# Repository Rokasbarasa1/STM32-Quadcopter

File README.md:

I am making a quadcopter from scratch (firmware including). This is the second step after my [Self balancing robot](https://github.com/Rokasbarasa1/ESP32-self-balancing-robot) project. It is still a work in progress, but a lot of the heavy lifting has already been done.

### Some features:
* Acro and Angle modes.
* GPS position hold flight mode (Work in progress).
* Altitude hold flight mode (Work in progress).
* Controled by my custom [Pi-pico based remote control](https://github.com/Rokasbarasa1/Pi-Pico-remote-control). 

### Sensors and hardware used for controller:
* Controller mcu - STM32F411
* Accelerometer + Gyro - MPU6050
* Magnetometer - MMC5603 (Used QMC5883 before)
* GPS - HGLRC M100 5883 (Used BN357 before)
* Barometer - MS5611 (Used BMP280 before)
* Radio link - RadioMaster RP1 2.4GHz ELRS (Work in progress)
* Debug Radio communication - NRF24l01
* Logging - [My custom STM32F411 based SD Logger](https://github.com/Rokasbarasa1/Logger). 

### Hardware of the drone itself:
* Motors - 4 x EMAX ECO II Series 2807 Motor
* ESC's - 4 x HGLRC 30amp 3-5S Dshot600 BLHeli_S 16.5 BB2 ESC (F-H-40 flashed with BlueJay 0.21.0V for BDshot600)
* Proppelers - 4 x HQProp DP 7x3.5x3 V1S 3 blade Propeller
* Battery - CNHL Black Series 3200mAh 14.8V 30C 4S (also used Turnigy 2200mAh 3S 25C)

# Latest flight video (January 2025)

# Pictures (Outdated)

### Checklist for going testing
* Drone frame
* Controller
* Controller antenna
* Propellers
* Sd card adapter
* Micro sd card
* Pliers 
* Wire cutters
* Screwdriver 
* Screwdriver bits
* Remote control
* Laptop
* Usb extension cable
* STM32 programmer
* Charged battery
* Battery checker

# Design documentation (work in progress)

## Code diagram

## Controller 

The controller is the main piece of the system. It is much more limited in what it can do than a normal computer, it is smaller, slower and resource constrained. So it cannot run a full GUI operating system. The good thing about them is that they are cheap and, depending on which one you get, just powerful enough to do interesting things. They are also cheap, I got mine for 7.28 USD. The microcontroller itself is just a chip on the breadboard. It is very self sufficient, sometimes you can just supply them stable power and they work fine. Like the attiny85 that just plugs into a breadboard. 

We need one that is more powerful than that so we will go with one called the STM32F411. ST(M)icroelectronics is the manufacturer, the 32 bit is how big data chunks the system can handle, and the F stands mainstream performance line of their chips, 411 is just a serial number for features. We dont really care about the features that much, it is maninstream so it will work for most things. 

I went with a ST microcontroller as it was one I had not used before. The chip on this one is very small so it is mounted on a pcb to seperate the tiny pins on the chip into big pins that we can use. The PCB that it is mounted on gives the microcontroller name blackpill because its a black pcb and its small. The pcb also has some extra features like voltage regulators to protect the chip, external oscillators to speed it up and leds to help us indicate status later. The pcb is so small that it lacks some quality of life features that a big pcb would have, like a programmer. The chip has to instead be programmed usng another product of ST called ST-link V2, which just converts a Usb interface to a programming interface for the stm32, it uses 4 pins to do that. This is negative of ST's products, other manufacturers dont have this problem with small pcb's, most of the time. The upside is you can debug the code with the same product, this is something that is painful on other microcontroller brands. The small form factor of the pcb is also very helpful for integrating the microcontroller into projects.

Each microcontroller manufacturer has their own "library" that abstracts the difficullt hardware drivers (HAL), on top of which the coding of the microcontroller can be done. In the case of the STM32 it is STM32Cube which lets you use C or C++ to write code for it. You can use Rust or anything else to write the code but then you are not using the manufacturers libraries and have to relly on open source. In my case I went with C as it is very simple and I can get great performance out of it. 

<!-- 
_The STM32F411 has a lot more GPIO than ESP32, which maybe has half of its pins unavailable and a bit more than the Pi-Pico on which a lot of the pins are grounds. Its also easier to mount on a breadboard than the ESP32._

_I hate the CubeMX code generation, feels like there is just junk in my repo. The alternative is really badly documented, to the point of needing to go into the library code to figure out how to use it. Feels like they skimped out on actual documentation to make you use the shitty code gen. Using the library code to figure something out is not easy either as there are multiple functions with similar names or functions that are depreceated. It always confusing to set anything up from scratch, like spi or i2c, there are so many functions that are supposed to do the exact same thing. By far the worst experiance of developing embededd software. Even fucking atmelavr felt like butter compared to this, though that might be a high bar in the embedded world. You cannot have development velocity in this ecosystem if you touch even a bit of the ST library. ESP32, Pi-pico and atmega are a lot better at this._

_Flashing the firmware on it is a lot easier though, in cases. If i was working on a breadboard, the Pi-pico would be a lot easier. When i made a protective cover for the controller part of the drone it was easy to press the pins of the programmer agains unsoldered holes of the pcb for programming. I did not have to fish for the 4 pins to attach too. This meant that sometimes the programming would not work, but overall it was a good experiance._

_For performance the STM32 is deffinetely not as fast as the ESP32, but it is fast enough, most of the performance is lost on sensor communication anyway._
-->

<!--
### Code design decisions

_The code looks not as a usual developers code looks like. I like having full names of the variables, no such bullshit as dT for delta time or whatever one letter variable. The same is for functions, full verbose names. I like to come back to old features and understand what is happenning. Lots of comments also._ 

_If there was a "Prettier" implementation for C (C code formaters are garbage, all of them) I would use it to enforce the same syntax everywhere, but there is not so there are gaps. I would love to enforce breaking of function variables if the developer has broken at least one, curly braces in line with for loops and if statments and functions.

_I tried to seperate the code into modules, of radio, data getting, motor control/pid and logging. They need to be moved to different files like controller/services/models architecture on backends, but at the moment it is just so much easier to have everything logic related in one file. In the future will be, main.c/business logic/drivers, with main.c only being able to reach drivers if it goes trough business logic. I come from full-stack development and we have much better understanding of code organization than embedded developers. The code will be seperated into seperate files once I am done with the project. I dont care about clean code, the functions will not be made 5 lines long._
-->

## Sensors drivers
To make our drone sense the world around it we need sensors. Based on the output of these sensors the code that i wrote in the microcontroller will make decisions and perform further actions to manipulate the environment it is in.

<!--
_A note about the sensor driver implementation. I continued the use of enums for defining the registers of the sensor and so on. Makes reading of the sensor code and even configuration of it a lot easier._

_Usage of macros for constant definitions is also done now. No more magic numbers, they have names now. Some pre division of these values is also done._
-->
### Supplying power to sensors
These sensors that we will talk about and hardware are meant to be powered some way, unless they have a battery on board them they have to have a physical connection to a power source. This is usually 2 wires, one for ground and one for most commonly 3.3V or 5V. A lot of the older snesors use 5V, these are usually the sensors made for the microcontroller called Arduino. These sensors need 5V because the old Arduino uses 5V logic(5V for a set bit and a 0V for a not set bit). If communication needs to be done to the sensor then there will always be a minimum of 2 wires or there can be more to accomodate different methods of sending or receiving information relating to the sensors. In the case where something has its own power source, and you know the power source or at least the interface that you will be using utilizes the voltage that is the same as you are using, then connecting the ground wire is enough. In fact if the device you are connecting to uses a different voltage than yours it is also safe to connect your ground to its ground. The important thing to match is the voltage lines, 5V, 12V, 15V.  

### Communcication to sensors
The sensors are just little microcontrollers in most cases, they have logic and interfaces that let the data be extracted from them digitally(toggling a single pin or more from 3.3v to 0V). There are sensors that are analog, but we are not using them, they are harder to work with. There are many methods of extracting the data out of sensors, these are called protocols. Each protocol has its advantages and disadvantages. Different combinations of, speed, wire count and complexity in setting it up. I will not be bothered to get into the details of how each protocol works as there are actual books for that. The best way to see how it works though is by getting thing called a "logic analyzer" and seeing for yourself how your hardware works.

#### I2C
I2C is one of the most convenient protocols to settup, it uses two wires, one for data and one for clock signal, it can also be chained to multiple sensors/device. Its fast enough and you can go above the recomended speeds if you believe in your hardware setup. I used I2C on my self-balacning robot project for sensors and it was fine. I did that again on this project and that was a mistake. You have to understand unless you are setting up something fancy to not have to do the communication to sensors synchronously, I2C can waste a lot of time by not being the fastest method.

I2c is very easy to setup though, and rarely ever causes problems. On the STM32 i did find that interrupts (will talk about these later) have to be disabled for the communication to not break. When it did break it would take 100ms to error out and continue with the program, essentially breaking the whole flow of the time sensitive program.

#### SPI
SPI is a lot harder to setup than I2c. The devices that can be communicated to using this have to have a slave select pin, that when 0V is applied to it means that the device is being communicated with. It also has 3 other pins, one for clock, one for data coming to slave and one for data coming to master. When you try to setup the hardware for a SPI connection, there is always something that just does not work. Its like having to plug in a usb, you always do it wrong way first. Sometimes the slaves/sensors have an extra pin that is also names similar to the slave select pin causing additonal confusion. The benefit of SPI is the speed it can reach, if you really need to be at the peak of performance then this is what you need. There are even variations of the protocol that use double or quadruple the pins amounts for the slave-master pins to multiply the transmission speed.

SPI is also a very simple protocol that you can even implement yourself. That cannot be said about I2C.

#### UART 
UART is the last protocol we actually care about and is one that is not normally used for sensors, but for transmitting text information or large amounts of data. It is also a very simple protocol, it uses 2 pins and does not use a clock pin. It  also cannot be chained like I2C and it is most importantly asynchronous by default. It is considered slower than the other protocols but it has benefits. It is reliable over long distances of wire and has recover mechanisms 

### I2C and sensors in general
For this communication we will use I2C. I2c is just a recipe (protocol) for what way to toggle the pins and in what order that both the controller trying to get the data (master) and the sensor (slave) understand and adhere to. There are other protoocls as well that the sensors support, like SPI, but I chose this one because it is easier to deal with. I2c uses only 4 wires, 2 for data. I2c is usually used for sensors or things that dont nescessarily need max speed in communication. You sacrifice speed for ease of communication.

### UART
Uart is another protocol for communication. It again uses 4 wires 

To do things with a sensor you need to read its datasheet. The most important part of which is the register map, it tells you where everything is stored and what register addresses you need to give to the sensor to read out the data from the registers. With i2c this often looks like sending the address of the register then reading the number of bytes you expect the data to be. Sometimes these sensors dont just automatically fill up their registers with data and you need to actually send commands that trigger actions that fill up populate those registers. Sometimes these commands just activate some special ability of the sensor. Thes sensors are almost always configurable in the same way also, by sending what register you want to fill up and then sending the bytes of data you want to put in that register. Configuring the sensor can be though of as having a wall of switches (the register map). There are as many rows of switches on it and the rows correspond to registers, each row has a number of switches that correspond to how large the register is in bits (most often its 8 bits). Each switch in the row does something, each one has a long description of its functionality in the datasheet. Some of the rows of switches you cannot manipulate as they are the ones storing the measurement that the sensor does, so the analogy falls appart there.

It should be noted that sensor data should never be taken as reliable data, the sensor data by default is always miscalibrated and has noise in it that makes judgements based on the data difficult. Each sensor type also has some problem that makes complex systems development difficult, but there are solutions to this, that we will talk about in sections "sensor fusion" and "filtering".

<!--
_I should have not used the I2c bus anymore in this project, for any of the sensors, its a bit too slow. I went above the recomended bus frequency though and reached 1.6 MHz but went down to 1.0 Mhz for stability just in case. That saved quite a of cpu time._
-->
# Gyro
The gyro can tell how fast the drone is rotating in each axis. If you tilt the drone 90 degrees to be on its side after it was standing flat on the ground and you do it immediately in one second the gyro will tell you that it degrees per second rotation is 90 on that axis you were rotating it around. To understand this, imagine a swing set attached to a metal pipe, the way the pipe is laying is some axis, lets say x, so the pipe is in line with the x axis. When you swing in the swing set you are really just rotating around the x axis of the pipe.

The gyro is the most important sensor for a drone. Depending on your requirements for the drone, it may be the only sensor you need, specifally for a mode control for the drone called acro mode. We will be implementing this mode of control but also more.
DRIFT

I am using the gyro on a sensor module called MPU6050. It is a common sensor, used on many drones. It actually has an accelerometer on it as well, but that is for later. The MPU6050 chip itself is mounted on a pcb that has voltage control stuff and power stabilization capacitors on it. This makes working with it easier, low risk of frying due to high voltage and it should be isolated from the power disturbances that can happen in an embedded system (these can just make the sensor not work very good). 

The sensor itself is configured by the code to be able to sense a max of 500 dps/s of rotation, which should be plenty for our drone if we dont plan to do spinny tricks in acro mode.

The gyro does have a problem. You may think if you keep summing the dps data over time, that you will get some data that tells you the orientation of the drone in 3D space, but that is not going to happen. The Gyro data is inherently noisy and if you sum it you will get values that drift over time. You can ease this noise issue by calibrating the gyro. Which is just reading maybe 1000 gyro values while sitting still and, finding the average gyro output value and then every time the you get the value out of the sensor you substract that average value from the data. This effectively removes some of the noise, but certainly not all of it. The next sensor will help deal with the noise issue.

### Accelerometer
The accelerometer can tell which way down is. You can imagine it like a a plank of wood in the air with a string tied to it and at the bottom of the string is a weight. As you move the the rotate the plank the string just keeps pointing to the ground. That is one property of the accelerometer, it can tell which way the ground is by displaying the force of gravity in G's split over 3 axies, x, y and z. So if the plank is at an angle to the ground, the G force will be split among the axies. If the plank is flat to the ground, only the z axis will have the value. If you make suddent movements and move some distance with the plank the weight will react to that and start to point away from down and will instead point slightly to the side. Using this you can sense when acceleration happens. This is where the analogy falls appart as the weigt will then have momentum, where as the real accelerometer will not be succeptible to that. When the acceleration stops the accelerometer will also stop being affected by it. 

So now we know which way is down and we know if we are accelerating in some direction.

The accelerometer also has some problems. If we want to use the data in any way on something that moves and can control itself we will always have parasitic accelerations as its just picks up every movement and creates more acceleration data. The accelerometer also needs calibration, its calibration is in part similar to the gyro, but can go further. The same average value calibration can be done when the drone is flat (extremely flat, like bubble level flat in both axies), this gives you the deviation form actual gravity. If any other axis than z has average values of more than 0.01 then that needs to be substracted from them. If the z axis is not exactly 1.0 G then it needs to also be substracted or added to to make it 1.0. This is the first level of calibration. 

The second level is a bit more complicated, it can happen that when you rotate and try to isolate the axies (make the value only show on one axis) that value can be not exactly 1.0. If you were to rotate the drone around for 5 minutes straight without introducing ANY acceleration but gravity and logged all of that data and plotted it in a python 3 dimensional graph, you would see either a sphere or a ellipsoid(squished sphere). The shpere means youre accelerometer is probably good to go, but even a slight ellipsoid squish means its bad. To fix this type of problem we need to use linear algebra and use matrix multiplications to transform the data into the sphere. For this I used a software called magneto12, I give it the raw values of the accelerometer and it calculates me how the modifications to the values. These calibrations are then applied every single tiem the acceleration data is gotten.

The accelerometer combined with the gyro though solves this issue. We will talk more about this later, but gyro+accelerometer can give us accurate data on our orientation for axies x and y, but not z. This data is enough to make a drone that has a flight mode called angle mode. The next sensor will solve that problem of the z axis.

The accelerometer we will be using is on the same chip as the gyro, the MPU6050. We will use the 2G range of readings for the accelerometer. Having a lower g value capture means there is more bits of data left for higher resolution value storage (higher resolution means you just have more digits after the decimal).

### Magnetometer
The magnetometer can sense the magnetic field of the earth, it gives these readings in micro teslas in 3 axies. That is as much as I know about how it works. The magnetometer can be used to always know in which direction is north, acting like a compass. You can use the relation to north to figure out which way you are facing or at least have a reference to where you were facing and which way you are facing now. The magnetometer is also essential if you want to use a GPS.

The magnetometer has some problems though, its data can be disturbed by magnetic fields of magnets and various metals. To use it, you need to always calibrate it, otherwise the data is useless. The calibration method is similar to the accelerometer calibration part 2. You collect a lot of data by rotating the drone in the air repeatedly, all kinds of loops, then you plug that inot magneto12 and you get two calibrations. A "hard-iron" calibration with 3 values and a "soft-iron" calibraiton with 9 values, really just a modified identity matrix. The "hard-iron" distortion is caused by magnets and the  calibration is just a offset of the value to center it around 0, similar to the gyro calibration. The "soft-iron" distortion is caused by various metals being around the sensor, it can also be characterized by the data not looking like a sphere but like a ellipsoid, just like the accelerometer one. It can also happen that you see a pancake in the "soft-iron" calibration, that means your sensor is not good and should be replaced, more on that later. All of these calibrations ideally have to be done outside in nature, far away from any disturbances. It is also very important that the drone is fully assembled when calibratin as each drone component can have some disturbance to the magnetometer.

I originally went with the QMC5883L magnetometer, it had a lot of problems with pancake graphs, but the ocasional one worked ok. When i started making my quadcopter I ripped the only working one that i had out of my self-balancing drone and it also turned into pancake. Eventually i had to get rid of all of them and just get a new sensor. I got the AdaFruit MMC5603 to replace it, origianlly I was really afraid that something was going to be wrong with it as the sensor chip was so tiny, but it was wrong and the sensor has so many more features. It is able to test the values it puts out itself and determine if something is wrong, set a data fetching rate, it can degauss itself which is amazing. Its such a great little sensor, it solves all of the problems i had with the magnetometers.

### UART

### GPS
The GPS is technically not a sensor but a receiver antena for sattalite signals, but I do like to call it a sensor. It picks up signals sent by sattalites of different constelations like GPS or Gallileo. It then uses the signals it receives and math to compute where it is on earth. The more sattalites it has the more accurate the calculation is. It outputs a lot of different data, but we primarilly care about about latitude, longitude, sattalite count and fix quality. The latitude is the vertical coordinate on the globe it increases or decreases when you go north or south, like y axis on a graph. The longitude is the horizontal coordinate and changes value when you go west or east, like x axis on a graph. The longitude is a special case, it is not linear like the latitude, it increases in precision when you go further away form the equator. This makes a bit difficult to work with as the code needs to use the linearized version of longitude, but to display the data you need to see it non linearly. The sattalite count is important to know the quality of data that is being delivered, a sattalite number of 10 or above is good quality. The fix type is a lower bar for quality, if the fix type is "3D" it is good enough quality to do some really bad gps position tracking or holding.

The gps can be used for a lot of things, but we are going to use it for position hold and maybe later for waypoint following.

### Barometer
The barometer can tell you how dense the air is. If you lift the drone up it will show lower pressure and if you lower it it will have higher pressure. The drone can sense the change in pressure and then convert that pressure change in to actual measurable change in altitude. This is essential for altitude hold functionality. 

There are problems though, a drone has propellers and propellers can generate wind and low pressure, the barometer can pick up this pressure change and provide fake data that will make the drone think the altitude is changing quicker that expected. Dealing with this is difficult. I have not progreessed far in this area yet, but I have tried to isolate the the sensor using foam and tape so cross wind cannot blow over it and aid can only come in from one side and the result was no improvement. Still some work left to be done

The sensor I chose first was the BMP280, which is a fine sensor and worked fine but I felt that it was not precise enough. I switched it out for the MS5611 which is widely used due to its accuracy. Barometers often come bundled with temperature sensors and even humidity sensors in some cases. These additional sensors aid in altitude calculations as then everything about the atmosphere that is important to altitude can can be sensed.

Calibration for barometers is done in the factory they were made in. The sensors registers hold the calibration data which is read on sensor initialization and applied once data is gotten. The MS5611 sensor is one of those sensors which you have to tell to start taking a data sample of either temperature or pressure and wait a bit until the data is ready. In our case we alternate between getting the temperature and pressure to have the most accurate altitude measurement in the end.

The altitude calculation can be done as an absolute altitude using formula to determine the current altitude from numbers purely. This altitude calculation is often best when setting a initial altitude by manually if it is known. This is good for devices that are intended to measure altitude in a human understandable way. The other options sampling pressure, setting that as the reference pressure and then always measuring the changes in altitude based on how far away it goes off the reference. This is effectively setting the sea level to be at the current pressure. It is useful for applications where you just want to know which way the altitude changed and that it is stable. This second option is what we use for our drone.

## Other hardware 

### A note about powering of hardware 
When i said that the 

### SPI
We talked about I2C before and how it is a protoco for communication, there is another one called

### Debug Radio
To actually communicate to the drone you need something that can pick up wireless signals. When I was making my self-balancing robot I create a remote control that had a radio transceiver(can send and receive radio signals) on it. So i chose to use the same setup on the drone.

A radio module is just like one of the sensors it communicates to the  

### Axies
Explain X Y and Z. 

BREADBOARD

### Old todo lists i will remove later

TODO after test 1:
* X Take off testing equipment as drone is too heavy to fly.
* X Uncomment second axis stabilization

TODO after test 2:
* X fix stuttering issue with motors. I think it is from receiving too little radio signals
* X figure out how to make screw nuts not undo themselves. Make the whole thing more rigid.
* X maybe upgrade to the extended range radio sensor
* X Make the robot turn off if it gets to an angle of like 45 degrees as that is not helping it hover

TODO after test 3:
* X Fix issues with remote restarting and roll joystick not making contact with pins.
* X Fix quadcopter event loop lag. Improve refresh rate of robot
* ! figure out how to use integral without super windup
* X remove comments from both remote and quadcopter.
* X add loop timing to remote to have constant refresh rate
* X Implement logging to sd card and log in a format that can be understood by something like betaflight blackbox analyzer
* X Make sure the motors never stop spinning at even at the lowest setting when controlled by the remote. This will help responsiveness.

TODO after test 4:
* ! Add blackbox logging for gps data
* X Find out how to adjust what pwm frequency the esc accepts and change it from 50Hz to as fast as possible.
* X The radio module caches the data sent durring the boot proccess of the quadcopter. Make sure the data is deleted before it gets to the pid loop as it is dangerous.
* X Recalibrate accelerometer because it was moved and reglued.

TODO after test 5:
* X Tie down new escs like the old ones were
* X Make sure the motor screws don't undo from vibrations
* X Mark the front and back of the drone
* ! Fix issues with magnetometer
* X Fix blackbox log roll log being opposite
* X Reduce angle of attack for pitch and roll

TODO after test 7:
* ! Fix issues with blackbox logging showing wrong motors spinning and wrong pitch and rol. All of them either inverted or showing up on the wrong motor.
* ! Find a new more reliable magnetometer
* X Attach an FPV camera for better orientation and control while flying.

TODO after test 8 (Crashed and broke a rotor leg):
* X Print new rotor leg parts
* X Resolder cut ESC wires
* X Flip degrees per second yaw control application to motors and reduce the gain.

TODO after test 9:
* ! Continue doing small tests to see which way the robot is leaning with no pitch or roll inputs to calibrate the accelerometer
* X Add accelerometer calibration tweaking to the remote control so the drone does not have to be reflashed every time
* ! Consider switching to the kalman filter for better sensor data

Test 10
The new feature of the remote control being able to change the accelerometer offsets was really good. I managed to get a general direction in which it needed to be adjusted, it always leaned right and a bit forward. I was not able to adjust it perfectly though as i ran into issues of my pid settings just not being good enough, P and D are no longer enough to keep good balance. The new flight mode did not work as expected, i set it lower than what is generally expected from it and i did see that it was not enough, i needed to make a big demand of 70 cm for it to star rising a bit, which was not good. Need to have more confidence in it to not go flying somewhere, but possibly try it more after i figure out balance on the mode 0 balance. Low pass filtering of the gyro and accelerometer did not really have a negative impact on the quadcopter. Tried playing around more with the integral with a bit of success in lowering the oscillation of the drone when balancing. Need to continue tests on a very flat surface next as moderately level ground is not enough anymore. The beta in the 

TODO after test 10
* Do more tests in flight mode 0 with integral and when a better balance PID is found adjust accelerometer offsets again.
* Add a note in the remote control accelerometer calibration screens what the impact of the calibration will be, like - +X = Pitch forward and so on.
* Compare to other quadcopter projects to see what i am missing to make things better.

Test 11
Realized that offsetting the actual accelerometer calibrations might not be the best way to fix the quadcopter balance point. Tried implementing a degrees offset for the pitch and roll of accelerometer but ran into issues of feedback loops once the offset is applied, making one or more motors spin faster and faster when idle on the ground until they shut off. Meaning that the gyro_degrees is affected in a feedback loop. (The feedback loop turned out to be related to the mpu6050 outputs of acceleration and gyro freezing)

TODO after test 11
* Figure out problem with feedback loop of offset degrees
* Replace MPU6050 with new sensor as this one is getting frozen sometimes. It is fine to use for testing now, but for extended flights in the future it will fall from the sky.

Test 12
I did some more tests and i found out that there is a problem with using calibration and filtering. If calibration was done on data that was not filtered and then the actual data used is the filtered one, the effect is that the calibration is useless. I have to either apply filtering on the sensor hardware level or use filtering everywhere in software including when calibration is done. Durring testing i saw that the gyro values post calibration were a constant 3 degrees/s which made half of the flight test useless as the battery was half drained. 

I also found that that the motor and prop vibrations really do affect the sensor readings a lot, i am surprised it even hovers a bit after looking at them at 40% throttle.

TODO after test 12
* ! Add material dampening of vibration
* ! Improve software filtering to remove what vibration was not already removed by material dampening.
* ! Test vibrations with fresh propellers.

Test 13
Tested the new low pass filtering on the drone. It worked very good at the 45Hz frequency setting, not so good at 22Hz or 10Hz with significant delay in response being visible. Did more tests on the yaw control functionality, it works very well now but there is a big drop in throttle when yawing with at a fast rate. The altitude hold functionality in flight mode 1 works better now but is still no good as i still need to put the throttle stick to 75% for it to do anything and lift off it does not keep the altitude at a neutral position. The balance correction is now easier with the low-pass filter but it still needs some work to find the sweet spot.

TODO after test 13
* ! Find out if the yaw control throttle issue with altitude could be solved or if that is just because my quadcopter does not have enough power in to keep altitude with two motors.
* ! Improve the offsets more on the next test.
* ! Find out why the altitude is not working so good.

Test 14
Got a better balance point but when testing the altitude hold broke one of the legs.

Test 15
Dialed in the altitude hold settings for PID, the quadcopter now holds altitude relatively well, but as it struggles to find a level offset it is not good to improve it more at the moment. The offsets still change a lot even with a low pass filter on, need to invest more in flight-controller dampening.

Test 16
Mounted new motors and tested them. Much less vibration as can be seen in the vibration profile for them. The quadcopter flies a bit better, but not as much change as i though it would have. I tried my best to balance it so it does not drift and got closer than the other motors, but did not get results that are much better. I am no longer even sure that this is a goal worth doing more tests for, and maybe i should just get the best stabilization i can and move on to perfecting the altitude hold and gps hold.

I tested it again the same day. Managed to improve the altitude hold functionality, by raising the integral gain 12 times I sped up the time it takes for it to charge up, so it reacts faster from ground launch. An issue is that raising the integral gain to charge it faster makes the integral give some overshoot to the vertical velocity target, for this i raised the proportional by 0.2 and got it to control a bit. Further testing is needed.

I did notice that with the new prop and motor combo the quadcopter does not have as much battery, so it means it is less efficient. This is expected as the propellers are smaller. I have also found that the new propellers are more durable than the ones i had before, maybe the decreased tip speed, material and shape of the tips plays a role in that. The quadcopter feels more loose with the new propellers, and that is not necessarily a good thing.

TODO after test 16
* ! Tighten all the nuts on the legs
* ! Find out why when gps is enabled the flight controller starts having a 140ms delay in sensor readings in I2C after the thing being on for a couple of minutes. 

Test 17

I have hit a dead end in testing. The drone is not supposed to handle this bad, vibration has been eliminated. I believe i am missing something big in regards to PID. I have seen others implement acro mode first and then feed that to implement angle mode. I am going to try to do the same as i have planned to implement acro mode anyway.

Test 18

I was correct in thinking something was missing. As soon as i started testing with pid as angle mode -> acro mode -> motors things started to work great. The drone now balances a lot better in angle mode and is very easy to control compared to before. Acro mode works ok, i can see some wobble as it wants to settle down to to a angular rate, which means there is more tunning to do. The next step will be to get the sd card blackbox logger working again, by fixing the hardware problem it has. Using the logger I will be able to see how it responds to setpoints over many different pid values for the acro mode and in that way i can figure out which one fits it best.

TODO after test 18
* X Fix the logger hardware problem.
* X Add more details to the betaflight log about the settings of the quadcopter, so that it allows the data to be analyzed more.
* X Make it so that when PID settings are changes, the quadcopter starts writing a new blackbox log file.
* X If the quadcopter starts a new log file it has to add the ending to the old one, so that opening it is easier on the computer.
* X Tune the blackbox log to the point that the log corresponds correctly to drone orientations
* ! Perform tests as in Chris Rossers's video on PID tunning.
* X Fix broken legs.
* ! Try flashing BlueJay to the ESC's to have rpm data from the esc's

Fix roll and pitch joystick
Fix scaling of ALL degree values
Fix right side motors not showing.
The fft graphs don't show throttle vs frequency noise plot. No Throttle detected

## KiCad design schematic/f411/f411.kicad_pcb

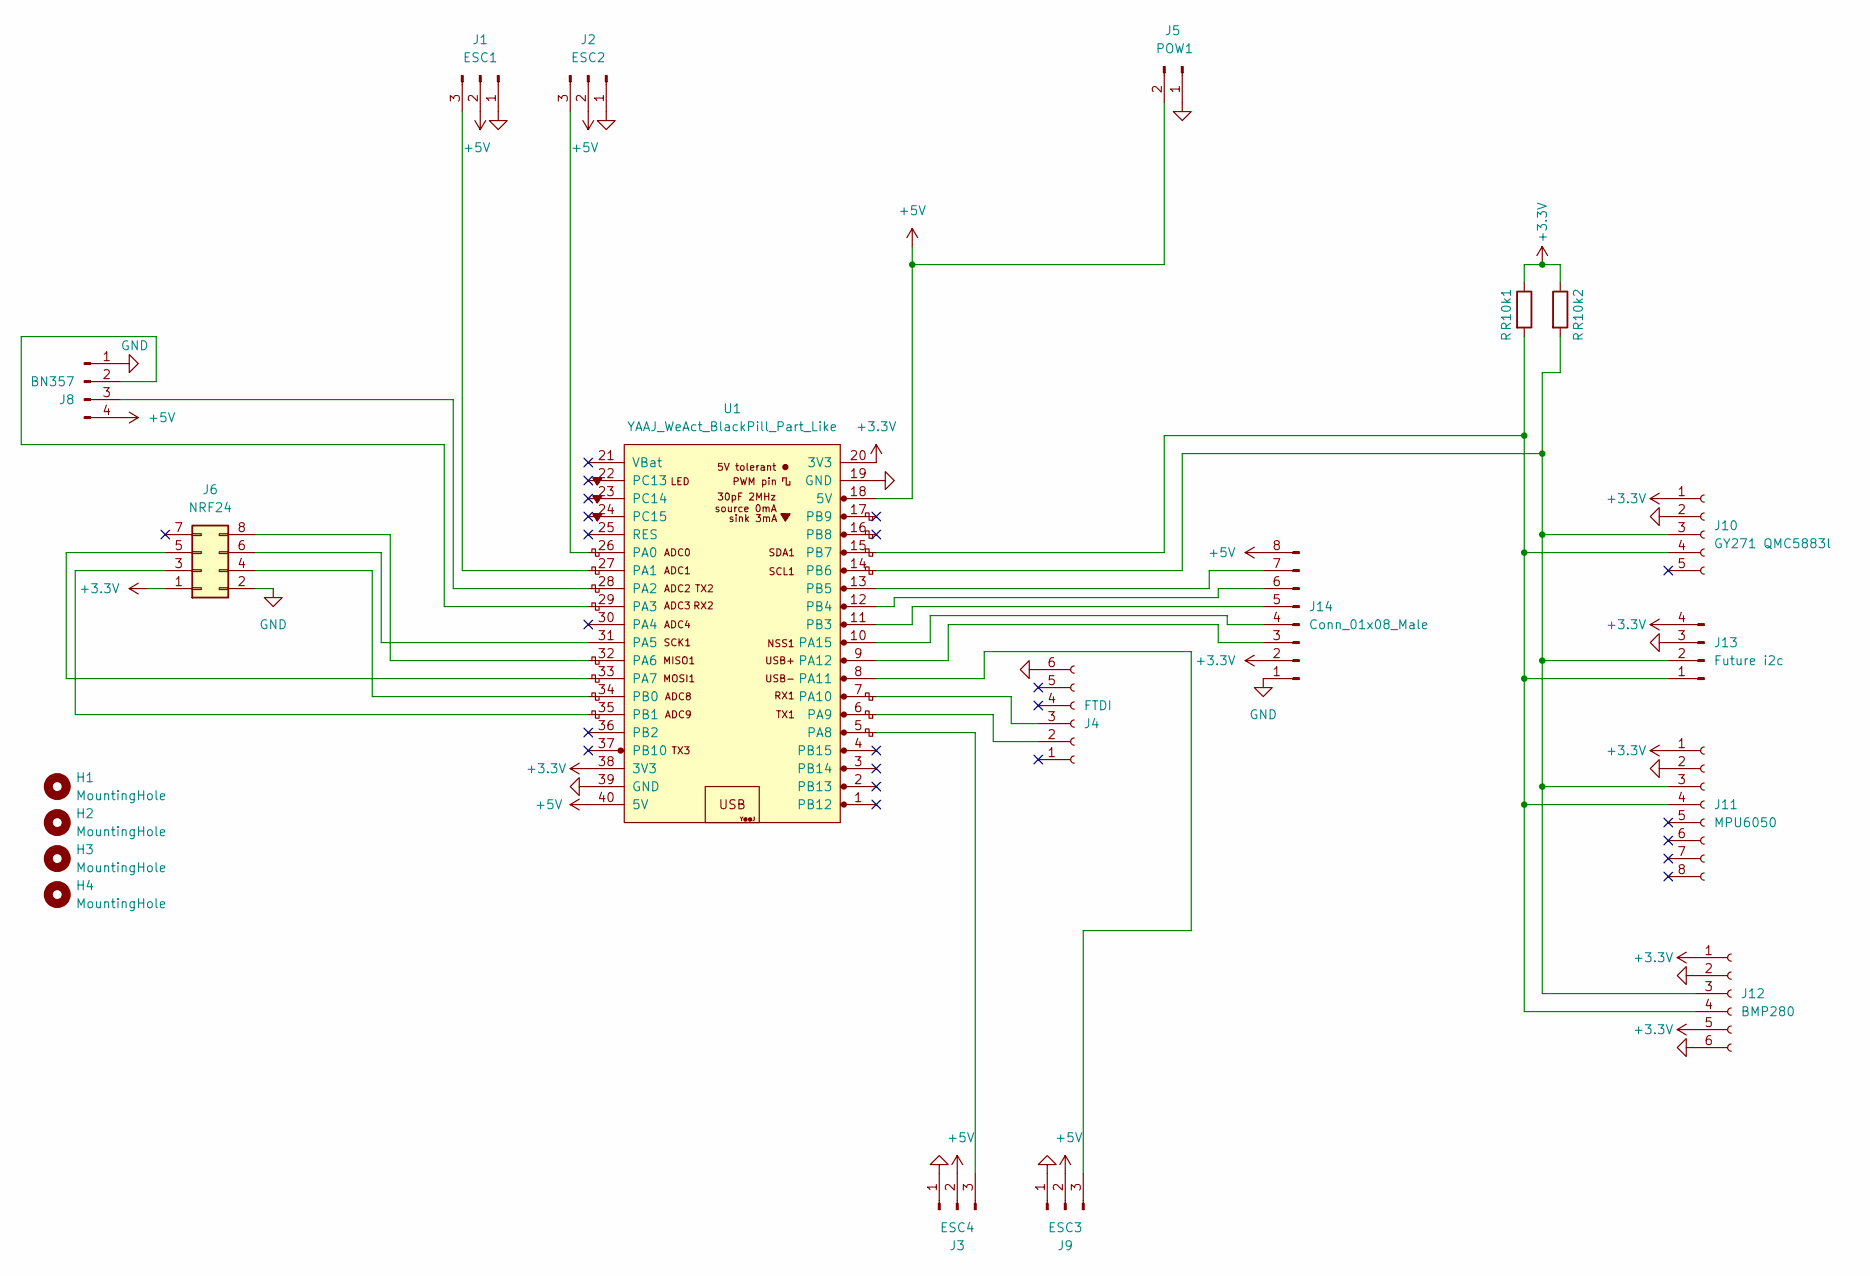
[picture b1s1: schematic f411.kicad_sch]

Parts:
H1, H2, H3, H4: MountingHole; MountingHole_4.3mm_M4
J1: ESC1; PinHeader_1x03_P2.54mm_Vertical
J2: ESC2; PinHeader_1x03_P2.54mm_Vertical
J3: ESC4; PinHeader_1x03_P2.54mm_Vertical
J4: FTDI; PinSocket_1x06_P2.54mm_Vertical
J5: POW1; PinHeader_1x02_P2.54mm_Vertical
J6: NRF24; PinSocket_2x04_P2.54mm_Vertical
J8: BN357; PinHeader_1x04_P2.54mm_Vertical
J9: ESC3; PinHeader_1x03_P2.54mm_Vertical
J10: GY271 QMC5883l; PinSocket_1x05_P2.54mm_Vertical
J11: MPU6050; PinSocket_1x08_P2.54mm_Vertical
J12: BMP280; PinSocket_1x06_P2.54mm_Vertical
J13: Future i2c; PinHeader_1x04_P2.54mm_Vertical
J14: Conn_01x08_Male; PinHeader_1x08_P2.54mm_Vertical
R10k1, R10k2: R; R_Axial_DIN0207_L6.3mm_D2.5mm_P10.16mm_Horizontal
U1: YAAJ_WeAct_BlackPill_Part_Like; YAAJ_WeAct_BlackPill_2

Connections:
+3.3V: J6.1, J10.1, J11.1, J12.1, J12.5, J13.4, J14.2, R10k1.1, R10k2.1, U1.20 (3V3), U1.38 (3V3)
+5V: J1.2, J2.2, J3.2, J5.2, J8.4, J9.2, J14.8, U1.18 (5V), U1.40 (5V)
GND: J1.1, J2.1, J3.1, J4.6, J5.1, J6.2, J8.1, J9.1, J10.2, J11.2, J12.2, J12.6, J13.3, J14.1, U1.19 (GND), U1.39 (GND)
unnamed: J1.3, U1.27 (PA1)
unnamed: J2.3, U1.26 (PA0)
unnamed: J3.3, U1.5 (PA8)
unnamed: J4.2, U1.6 (PA9)
unnamed: J4.3, U1.7 (PA10)
unnamed: J8.2, U1.29 (PA3)
unnamed: J8.3, U1.28 (PA2)
unnamed: J9.3, U1.8 (PA11)
unnamed: J10.3, J11.3, J12.3, J13.2, R10k2.2, U1.14 (PB6)
unnamed: J10.4, J11.4, J12.4, J13.1, R10k1.2, U1.15 (PB7)
unnamed: J14.3, U1.9 (PA12)
unnamed: J14.4, U1.10 (PA15)
unnamed: J14.5, U1.11 (PB3)
unnamed: J14.6, U1.12 (PB4)
unnamed: J14.7, U1.13 (PB5)
unnamed: J6.6, U1.31 (PA5)
unnamed: J6.8, U1.32 (PA6)
unnamed: J6.5, U1.33 (PA7)
unnamed: J6.4, U1.34 (PB0)
unnamed: J6.3, U1.35 (PB1)

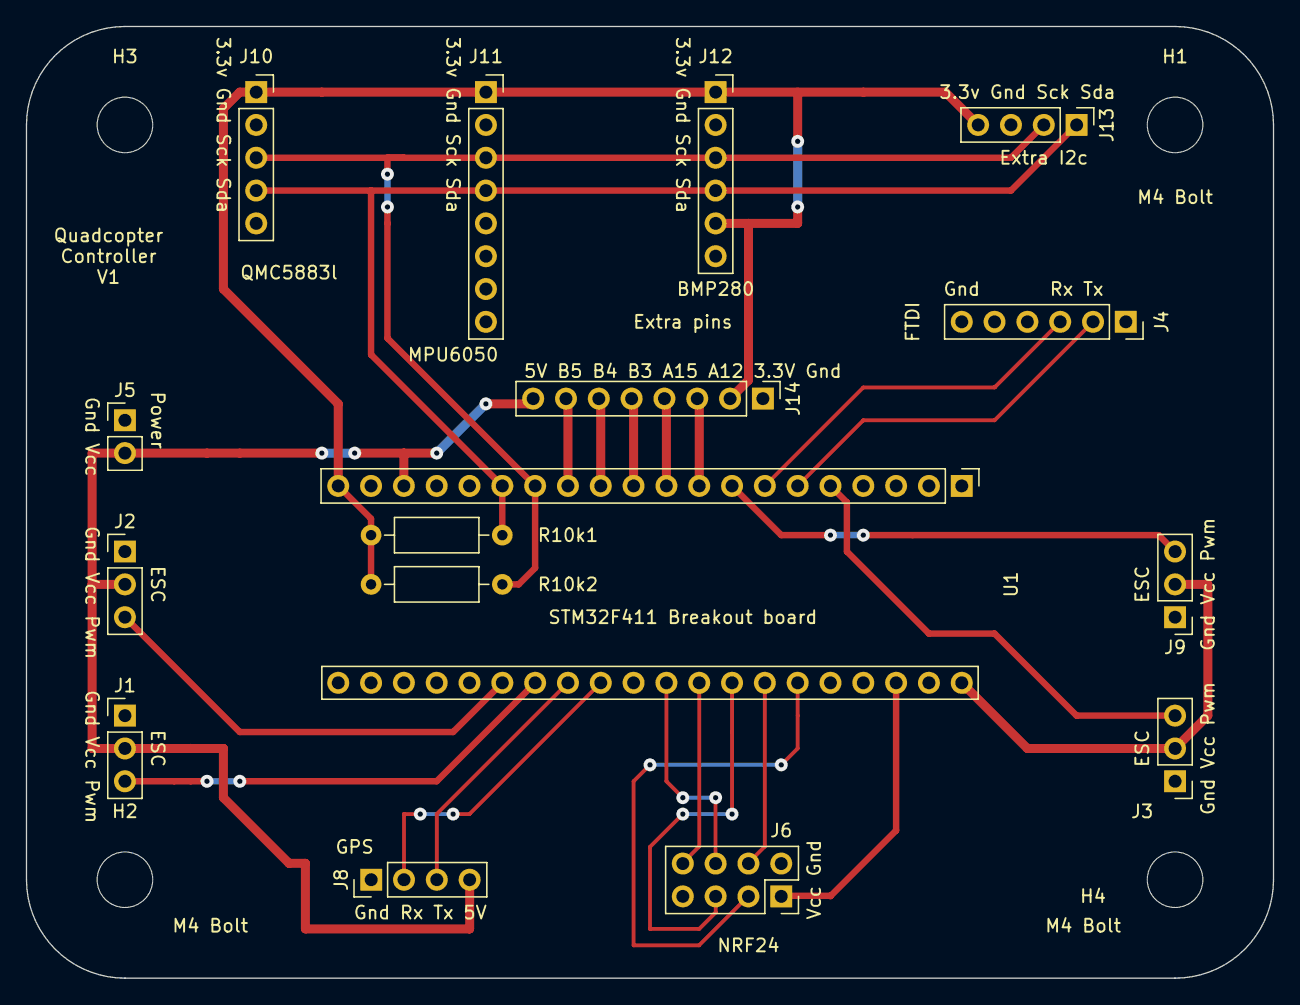
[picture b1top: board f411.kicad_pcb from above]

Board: 2 copper layers, 96.5 x 73.7 mm, 20 parts (0 on the bottom side), 23 nets.

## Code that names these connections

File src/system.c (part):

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#include "../lib/.layers/time_keeping/time_keeping.h"

// bdshot600 pins
// PA8  - TIM1_CH1 for motor back-left (BL)
// PA11 - TIM1_CH4 for motor back right (BR)
// PA1  - TIM2_CH2 for motor front left (FL)
// PB10 - TIM2_CH3 for motor front right (FR)

// UART pins
// PA2  UART2 tx GPS
// PA3  UART2 rx GPS
// PA10 UART1 rx FTDI
// PA9  UART1 tx FTDI

// I2C pins
// PB7  I2C1 SDA
// PB6  I2C1 SCL

// GPIO
// PC13 Internal LED
// PA12 LED

// SPI3 SD card logger
// PB5 MOSI
// PB4 MISO
// PB3 SCK
// PA15 CS
// PA12 Slave ready. Falling interrupt

// SPI1 Radio module
// PA5 SCK
// PA6 MISO
// PA7 MOSI
// PB1 CS 
// PB0 CE

// DMAs used. They have to not be reused otherwise problems
// TIM2_CH3 DMA1 stream 1
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
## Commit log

2022-11-02 Init
2022-11-13 Add mpu6050, gy271 and bmp280
2022-11-13 Remove example library
2022-11-20 Move cubemx files
2022-11-26 Added pwm and nrf24
2022-12-03 Added schematic and pcb
2022-12-21 Add error handling for uart 2
2022-12-28 Add generator files and fixes for modules
2022-12-28 Add generator
2023-03-02 Testing shit
2023-03-02 Fixing and simplifying bmp280 sensor values
2023-03-02 Remove old macro
2023-03-04 Improve bmp280 and gy271 sensor drivers
2023-03-05 Fixing multiple sensors and cleaning up the drivers
2023-03-07 Better documentation of nrf24l01 and communication speed increase
2023-03-19 Fixed gps data and bmp280 relative altitude measurement
2023-03-19 Push changes
2023-03-19 Fix sea level set altitude measurement
2023-03-19 Rearange code
2023-04-23 Add pid abstraction
2023-05-08 Sensor fusion fix for accurate gyro and pid for upright position
2023-05-08 Fix for sensor fusion again
2023-05-08 Fix for sensor fusion again again
2023-05-16 Testing motor max min calibration
2023-05-18 Changes to pwm frequency
2023-05-21 Add testing pid settings
2023-07-09 Add proper data reading rom remote controller
2023-07-22 Rename mpu6050 stuff
2023-12-05 Update with changes from self balancing robot
2023-12-20 Update code for first test flight with pid
2024-02-05 increase resolution of the data from remote
2024-03-25 Changes so far
2024-03-25 FIx issues
2024-03-25 Fix sd master not waiting for sd slave to be available
2024-03-25 Working old file detection
2024-03-26 Working writing to file
2024-03-28 Working special mode writing
2024-03-28 Clean up old logging code, increase logging amount
2024-03-30 Working async sd data writing at 83 Hz
2024-03-31 Remove unneeded code, add time tracking to each loop iteration
2024-04-28 SD logging at 139 Hz
2024-04-28 Generator content
2024-04-28 Initialized dma for async write but only sending 2 bytes with the rest zeros
2024-04-29 Changes that speed up sd to 234 Hz
2024-04-29 Comment out debug code
2024-05-05 Adding more info about robot
2024-06-01 Betaflight Blackbox logging added
2024-06-01 Fix led indicator
2024-06-04 Fix pwm value and 4 test
2024-06-15 Partial implementation for gps blackbox logging
2024-07-07 Status update
2024-07-29 Accelerometer calibration, new sensor fusion and data filtering
2024-07-30 Kalman filter altitude and vertical velocity
2024-08-05 Improving low-pass filtering of accelerometer and gyro data
2024-08-05 Push
2024-08-08 New magnetometer and corrected vertical velocity pid
2024-08-12 Gps config and vibration testing
2024-08-13 GPS changes
2024-08-14 Fixing roll, pitch and yaw values. Made yaw tilt compensation work
2024-08-14 Fix remote control inputs to motors
2024-08-14 Fix initial state function
2024-08-16 GPS PID adjustment
2024-08-27 Testing gps hold, before replacing the motors
2024-08-30 Old motor vibration testing
2024-09-10 Testing new motors
2024-09-17 New PID plan and flight test 18
2024-09-22 New logging features
2024-09-25 Update README.md with new video
2024-09-27 DSHOT600 and BlueJay
2024-10-09 Add Bidirectional DSHOT600 functionality, fix issue with i2c freezing
2024-10-11 Optimize sd card writing. Bump clock speed to 100Mhz. Break bdshot600
2024-10-12 Update timing of bdshot600
2024-10-12 Fix bdshot600 with 100MHz system clock
2024-10-14 520 Hz control loop
2024-10-15 Switch from milliseconds timing control to microseconds
2024-10-28 bdshot600 dma and performance optimizing
2024-11-27 RPM filtering and performance optimizing
2024-12-07 Test 25 corrections
2024-12-07 Fixing issue with changing accelerometer offsets freezing the controller
2024-12-21 Flight 30 changes
2025-01-18 Angle mode testing done, gps testing not done
2025-01-20 Gps logging and target setting features
2025-01-27 New GPS and barometer
2025-01-27 Add control over gps and altitude pid trough remote
2025-02-17 Fixes for altitude and gps before fligh 45
2025-02-19 Improve nrf24l01 data quality
2025-02-23 Swapped broken mpu6050, new gps hold roll pitch ratio
2025-03-18 Drone flight 52
2025-04-06 Flight 55
2025-05-03 Simulator for gps logic and fix for gps logic
2025-05-04 example data
2025-05-08 Latest changes of gps
2025-05-31 Latest changes. Kind of working gps targeting
2025-06-15 Latest code
2025-07-18 New gps logic and new yaw sensor fusion
2025-08-21 Testing new magnetometers
2025-08-26 Add new magnetometer
2025-09-13 latest working magnetometer test with compass motor frequency calibration
2025-09-19 Before restructure
2025-09-22 Split code sections into separate files
2025-09-22 Code diagram
2025-09-22 New diagram
2025-09-26 Add dynamic getting of declination based on wmm and gps data
2025-10-01 Improve gps position hold
2025-11-03 Latest mess in magnetometer
2025-11-04 Update mag calibrations
2025-11-12 Working rotation matrix and tilt compensation
2025-11-21 Adjust calibration
2025-11-24 latest tools
2026-02-28 Slighly working gps position hold

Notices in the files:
schematic/f411/f411.kicad_pcb:
creativecommons.org/licenses/by/4.0
License: CC BY 4.0
